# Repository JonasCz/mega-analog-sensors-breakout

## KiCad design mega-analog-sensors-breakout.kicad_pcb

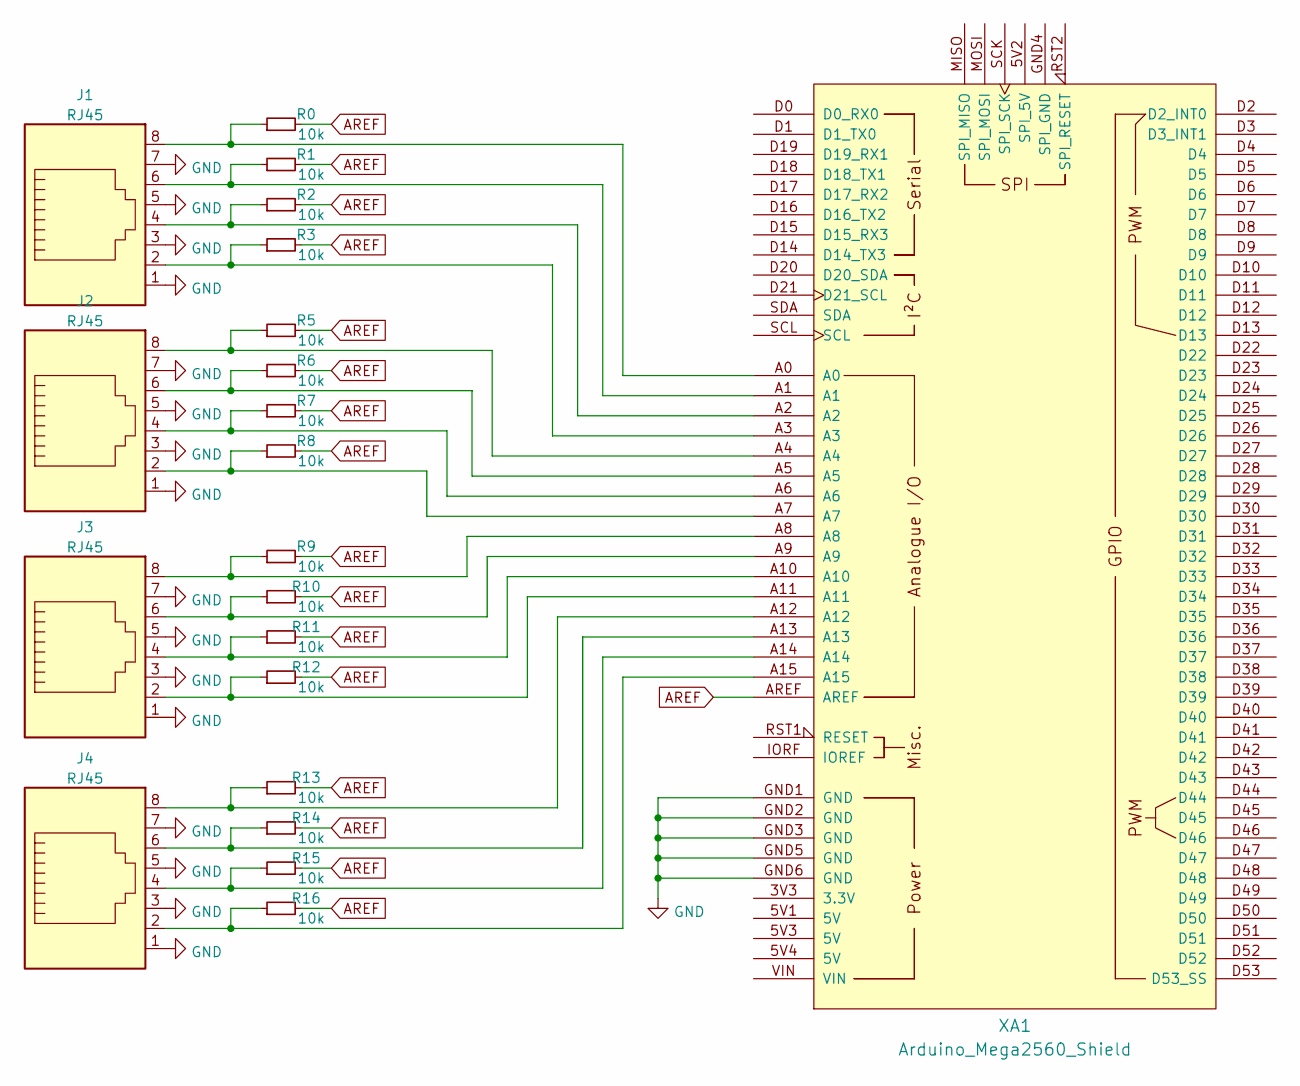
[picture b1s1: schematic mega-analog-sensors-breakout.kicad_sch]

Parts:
J1, J2, J3, J4: RJ45; RJ45_Ninigi_GE
R0, R1, R2, R3, R5, R6, R7, R8, R9, R10, R11, R12, R13, R14, R15, R16: 10k; R_0603_1608Metric
XA1: Arduino_Mega2560_Shield

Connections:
AREF: R0.2, R1.2, R2.2, R3.2, R5.2, R6.2, R7.2, R8.2, R9.2, R10.2, R11.2, R12.2, R13.2, R14.2, R15.2, R16.2, XA1.AREF
GND: J1.1, J1.3, J1.5, J1.7, J2.1, J2.3, J2.5, J2.7, J3.1, J3.3, J3.5, J3.7, J4.1, J4.3, J4.5, J4.7, XA1.GND1 (GND), XA1.GND2 (GND), XA1.GND3 (GND), XA1.GND5 (GND), XA1.GND6 (GND)
unnamed: J2.2, R8.1, XA1.A7
unnamed: J2.4, R7.1, XA1.A6
unnamed: J2.6, R6.1, XA1.A5
unnamed: J2.8, R5.1, XA1.A4
unnamed: J3.2, R12.1, XA1.A11
unnamed: J3.4, R11.1, XA1.A10
unnamed: J3.6, R10.1, XA1.A9
unnamed: J3.8, R9.1, XA1.A8
unnamed: J1.2, R3.1, XA1.A3
unnamed: J4.8, R13.1, XA1.A12
unnamed: J4.6, R14.1, XA1.A13
unnamed: J4.4, R15.1, XA1.A14
unnamed: J4.2, R16.1, XA1.A15
unnamed: J1.8, R0.1, XA1.A0
unnamed: J1.6, R1.1, XA1.A1
unnamed: J1.4, R2.1, XA1.A2

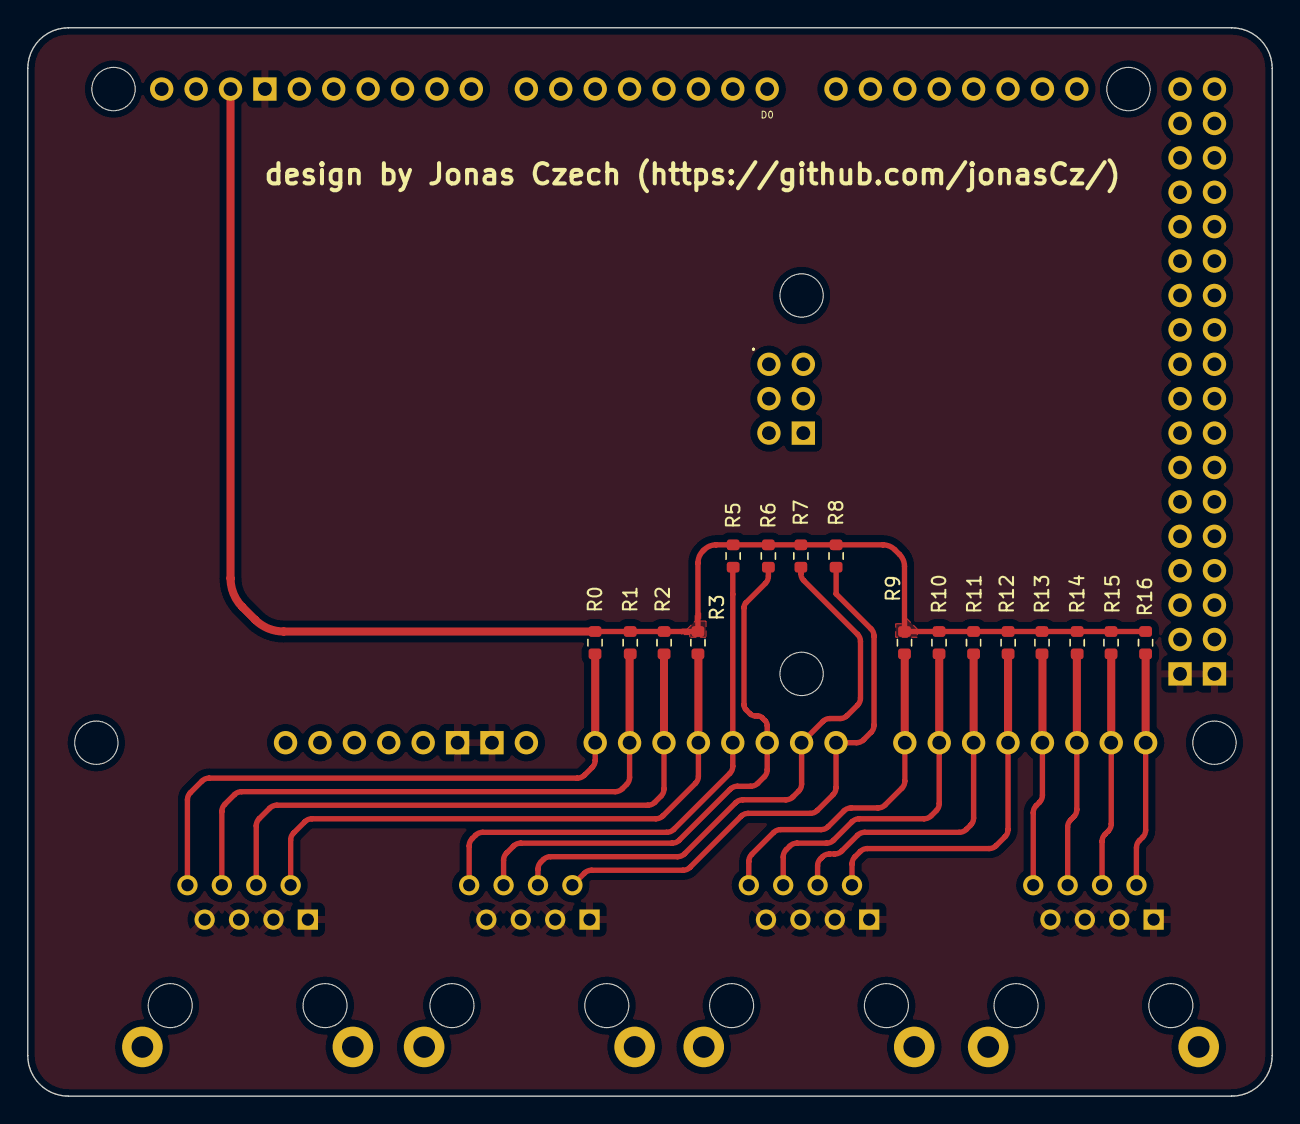
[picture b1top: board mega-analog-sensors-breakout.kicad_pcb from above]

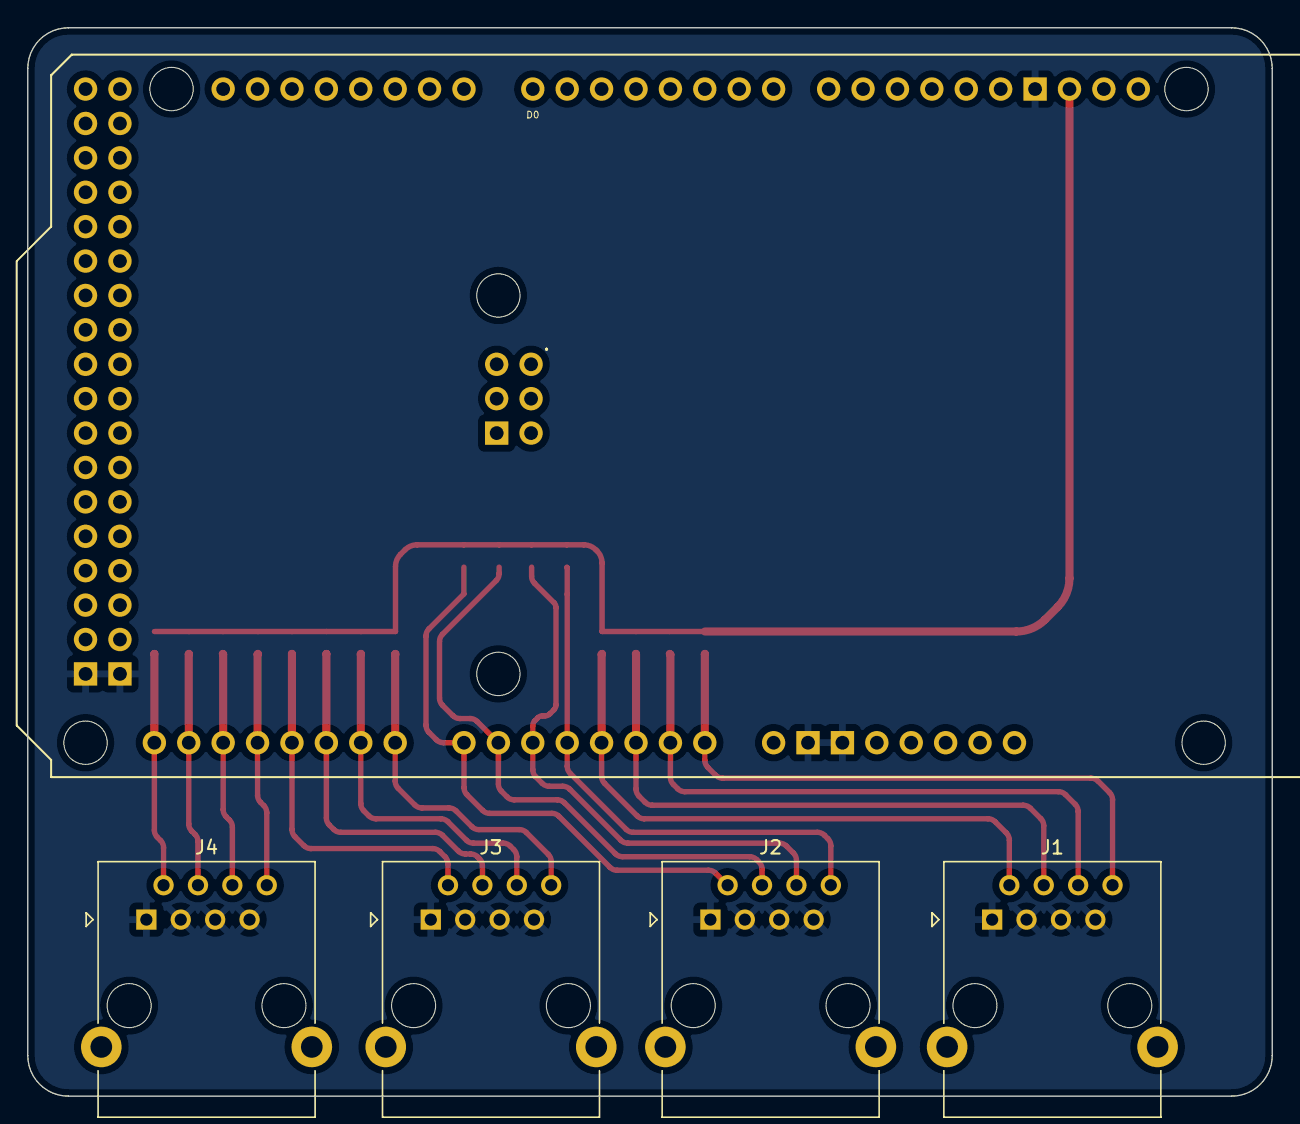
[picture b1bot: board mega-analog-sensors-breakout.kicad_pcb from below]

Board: 2 copper layers, 91.9 x 78.9 mm, 21 parts (4 on the bottom side), 18 nets.
